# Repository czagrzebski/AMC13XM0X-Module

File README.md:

# AMC13XM0X-Module for Industrial Sensors

A PCB design for the [TI AMC13XM0X](https://www.ti.com/product/AMC131M02) $\Delta\Sigma$ ADC module. The module is designed to interface with industrial sensors that support 0-10V or 4-20mA output. This module features a voltage and current sensing network connected to the differential inputs of the ADC. The module is designed to be used over Serial Peripheral Interface (SPI) communication protocol. 

The module features a 4-layer PCB design with a 2.54mm pitch header for interfacing with the host controller. The module is powered by a 3V3 supply. The module is designed to be used in industrial applications where high accuracy and reliability are required. The module is designed to be used with the TI AMC13XM0X $\Delta\Sigma$ ADC.

# AMC13XM0X ADC Overview

The AMC13XMOX $\Delta\Sigma$ ADC is a high-precision, power isolated, simultaneous-sampling, 24-bit ADC. The AMC13XM02 features a fully integrated isolated DC/DC converter that allows single-supply operation from the low-side of the device. The reinforced and capactive isolation barrier is certified according to VDE V 0884-17 and UL1577. The isolation barrier is made of a $SiO_2$ barrier that provides $7070-V_{PEAK}$ reinforced isolation, per DIN EN IEC 60747-17.

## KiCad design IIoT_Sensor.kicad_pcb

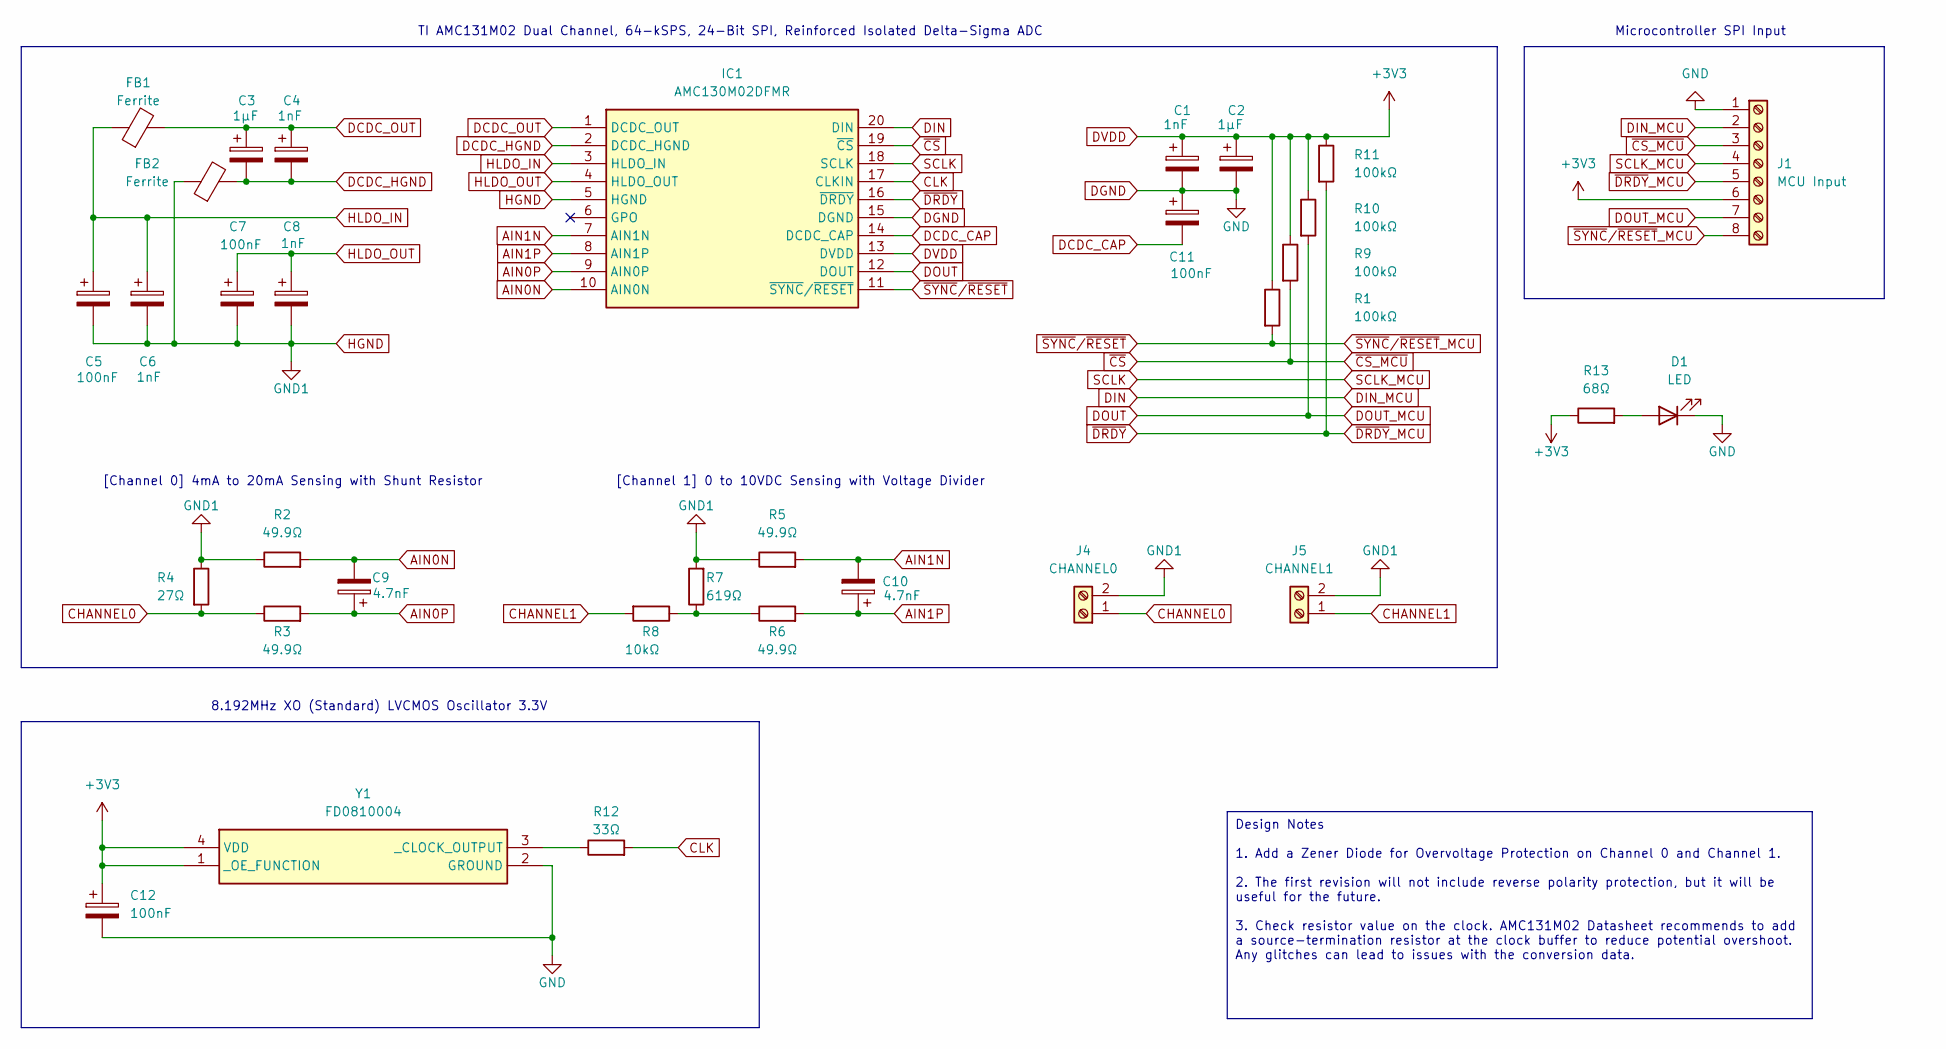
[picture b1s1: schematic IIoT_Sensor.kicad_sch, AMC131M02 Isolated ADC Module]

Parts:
C1, C4, C6, C8: 1nF; R_0805_2012Metric; DigiKey_Part_Number 399-C0805C102K5RAC7800CT-ND
C2, C3: 1µF; R_0805_2012Metric; DigiKey_Part_Number 1276-1029-1-ND
C5, C7, C11, C12: 100nF; R_0805_2012Metric; DigiKey_Part_Number 311-1140-1-ND
C9, C10: 4.7nF; R_0805_2012Metric; DigiKey_Part_Number 490-3044-1-ND
D1: LED; R_0805_2012Metric; DigiKey_Part_Number 732-4985-1-ND
FB1, FB2: Ferrite; R_0805_2012Metric; DigiKey_Part_Number 732-1608-1-ND
IC1: AMC130M02DFMR; Mouser Part Number 595-AMC130M02DFMR
J1: MCU Input; PinHeader_1x08_P2.54mm_Vertical; DigiKey_Part_Number 732-5321-ND
J4: CHANNEL0; CUI_TB001-500-02BE; DigiKey_Part_Number 102-6134-ND
J5: CHANNEL1; CUI_TB001-500-02BE; DigiKey_Part_Number 102-6134-ND
R1, R9, R10, R11: 100kΩ; R_0805_2012Metric; DigiKey_Part_Number 311-100KCRCT-ND
R2, R3, R5, R6: 49.9Ω; R_0805_2012Metric; DigiKey_Part_Number P49.9CCT-ND
R4: 27Ω; R_0805_2012Metric; DigiKey_Part_Number 311-27.0CRCT-ND
R7: 619Ω; R_0805_2012Metric; DigiKey_Part_Number 311-619CRCT-ND
R8: 10kΩ; R_0805_2012Metric; DigiKey_Part_Number P10KDACT-ND
R12: 33Ω; R_0805_2012Metric; DigiKey_Part_Number 541-33.0CCT-ND
R13: 68Ω; R_0805_2012Metric; DigiKey_Part_Number 541-CRCW080568R0FKEACCT-ND
Y1: FD0810004; Mouser Part Number 621-FD0810004

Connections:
AIN0N: C9.2, IC1.10 (AIN0N), R2.2
AIN0P: C9.1, IC1.9 (AIN0P), R3.2
AIN1N: C10.2, IC1.7 (AIN1N), R5.2
AIN1P: C10.1, IC1.8 (AIN1P), R6.2
CHANNEL0: J4.1, R3.1, R4.2
CHANNEL1: J5.1, R8.2
CLK: IC1.17 (CLKIN), R12.2
DCDC_CAP: C11.2, IC1.14 (DCDC_CAP)
DCDC_HGND: C3.2, C4.2, FB2.2, IC1.2 (DCDC_HGND)
DCDC_OUT: C3.1, C4.1, FB1.2, IC1.1 (DCDC_OUT)
DGND: C1.2, C2.2, C11.1, C12.2, D1.1 (K), IC1.15 (DGND), J1.1, Y1.2 (GROUND)
DIN: IC1.20 (DIN), J1.2
DOUT: IC1.12 (DOUT), J1.7, R10.2
DVDD: C1.1, C2.1, C12.1, IC1.13 (DVDD), J1.6, R1.1, R9.1, R10.1, R11.1, R13.1, Y1.1 (_OE_FUNCTION), Y1.4 (VDD)
HGND: C5.2, C6.2, C7.2, C8.2, FB2.1, IC1.5 (HGND), J4.2, J5.2, R2.1, R4.1, R5.1, R7.2
HLDO_IN: C5.1, C6.1, FB1.1, IC1.3 (HLDO_IN)
HLDO_OUT: C7.1, C8.1, IC1.4 (HLDO_OUT)
unnamed: D1.2 (A), R13.2
unnamed: R6.1, R7.1, R8.1
unnamed: R12.1, Y1.3 (_CLOCK_OUTPUT)
SCLK: IC1.18 (SCLK), J1.4
~CS_MCU: IC1.19 (~CS), J1.3, R9.2
~DRDY: IC1.16 (~DRDY), J1.5, R11.2
~SYNC/~RESET: IC1.11 (~SYNC/~RESET), J1.8, R1.2

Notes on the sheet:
Design Notes 1. Add a Zener Diode for Overvoltage Protection on Channel 0 and Channel 1. 2. The first revision will not include reverse polarity protection, but it will be useful for the future. 3. Check resistor value on the clock. AMC131M02 Datasheet recommends to add a source-termination resisto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
8.192MHz XO (Standard) LVCMOS Oscillator 3.3V
[Channel 0] 4mA to 20mA Sensing with Shunt Resistor
[Channel 1] 0 to 10VDC Sensing with Voltage Divider
TI AMC131M02 Dual Channel, 64-kSPS, 24-Bit SPI, Reinforced Isolated Delta-Sigma ADC
Microcontroller SPI Input

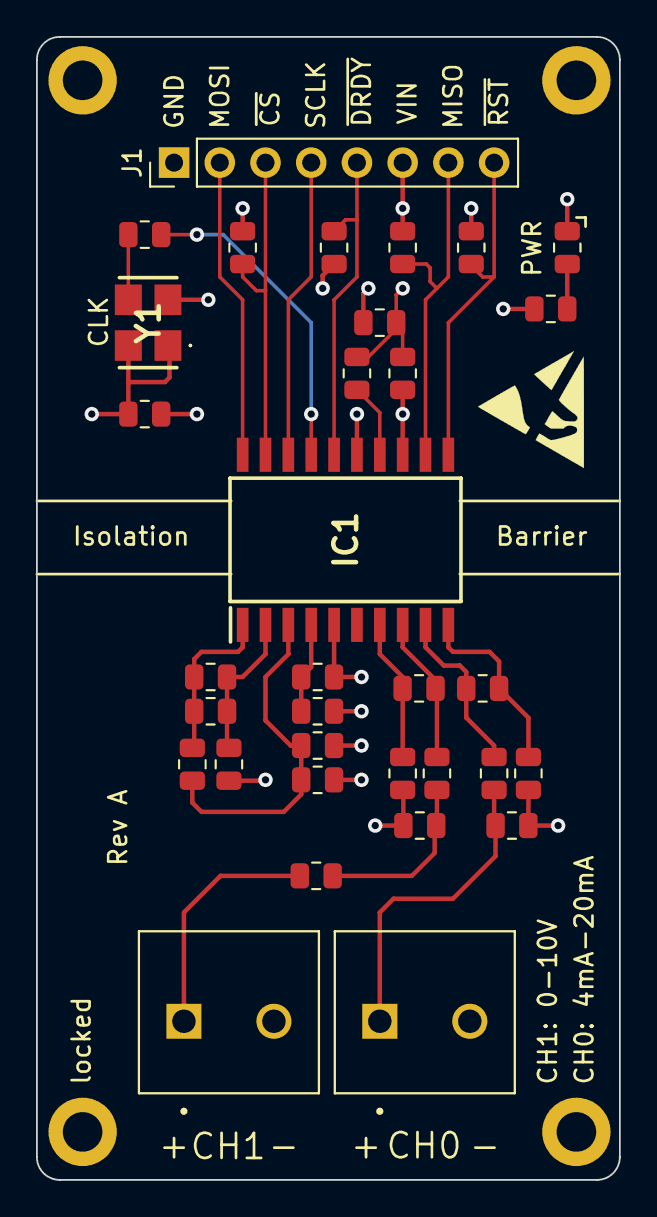
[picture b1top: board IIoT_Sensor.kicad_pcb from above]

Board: 4 copper layers, 32.4 x 63.5 mm, 33 parts (0 on the bottom side), 24 nets.

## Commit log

2024-03-30 init
2024-04-03 file organization
2024-04-03 added pics
2024-04-03 fixed text
